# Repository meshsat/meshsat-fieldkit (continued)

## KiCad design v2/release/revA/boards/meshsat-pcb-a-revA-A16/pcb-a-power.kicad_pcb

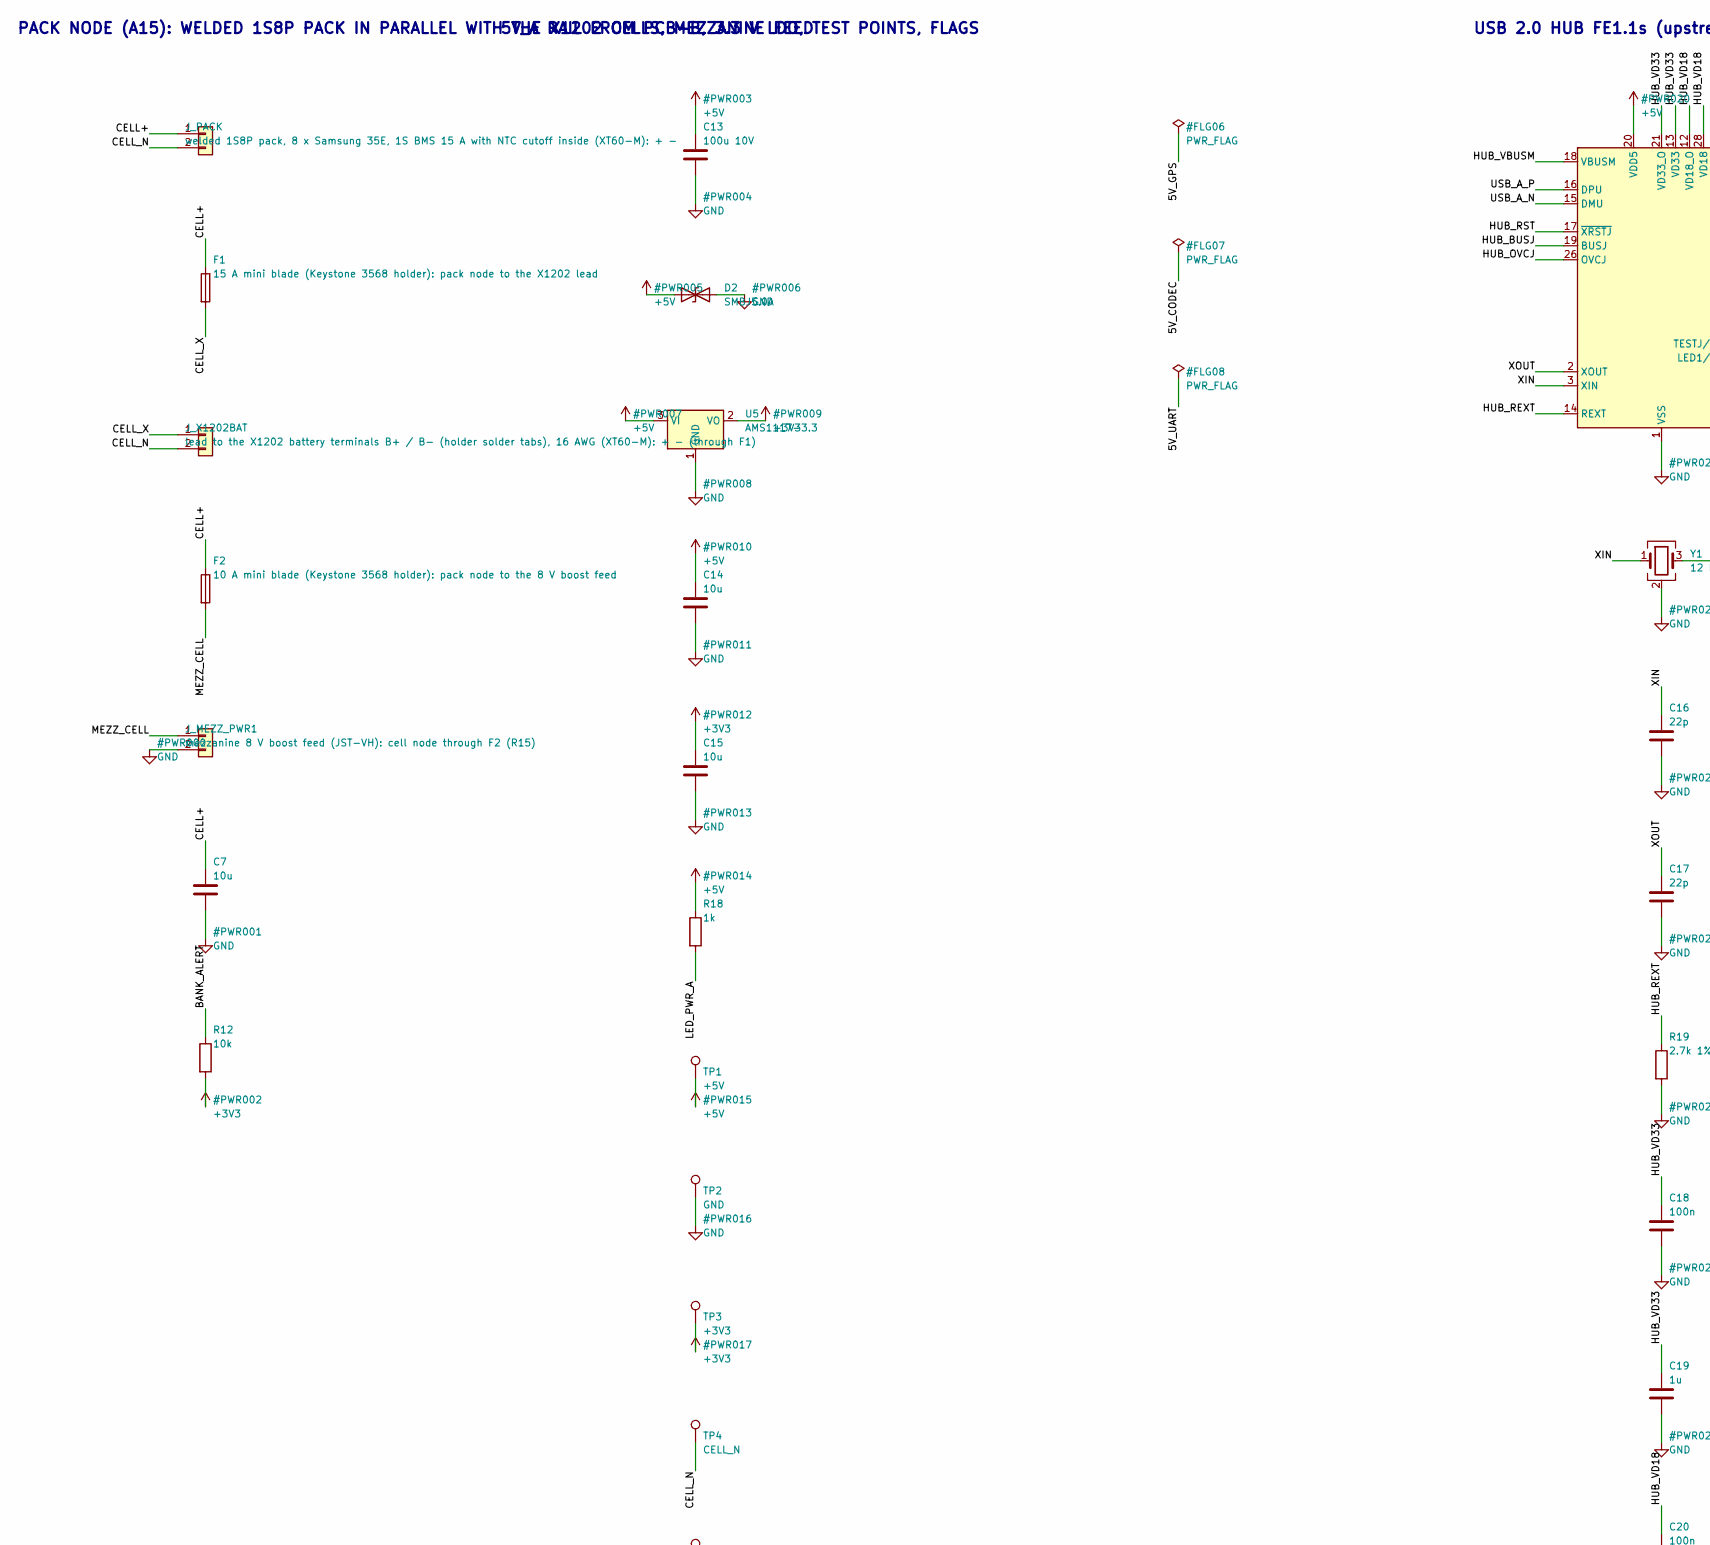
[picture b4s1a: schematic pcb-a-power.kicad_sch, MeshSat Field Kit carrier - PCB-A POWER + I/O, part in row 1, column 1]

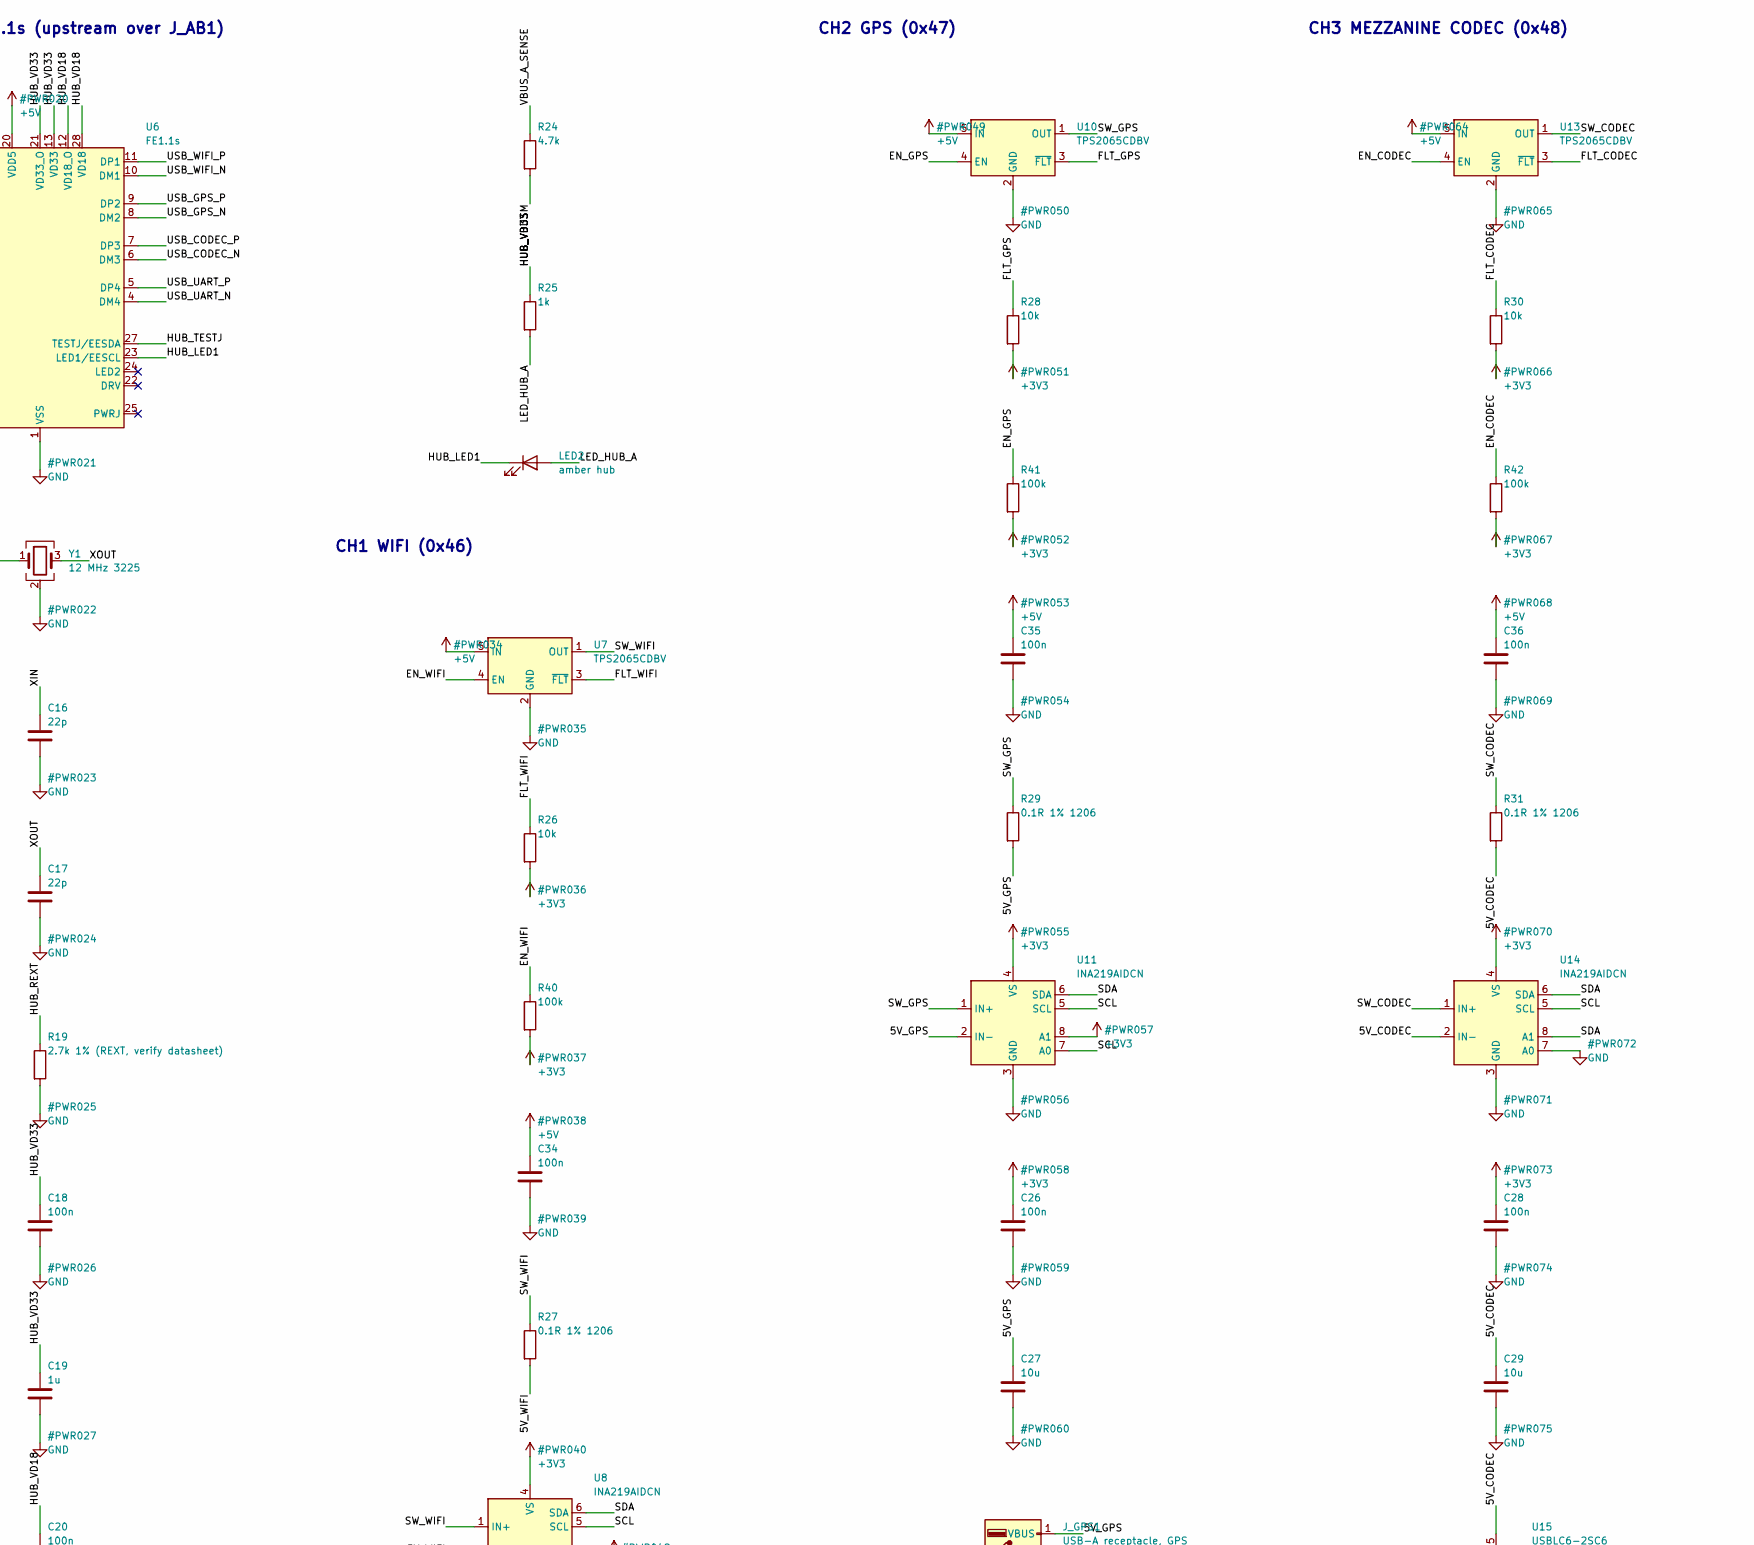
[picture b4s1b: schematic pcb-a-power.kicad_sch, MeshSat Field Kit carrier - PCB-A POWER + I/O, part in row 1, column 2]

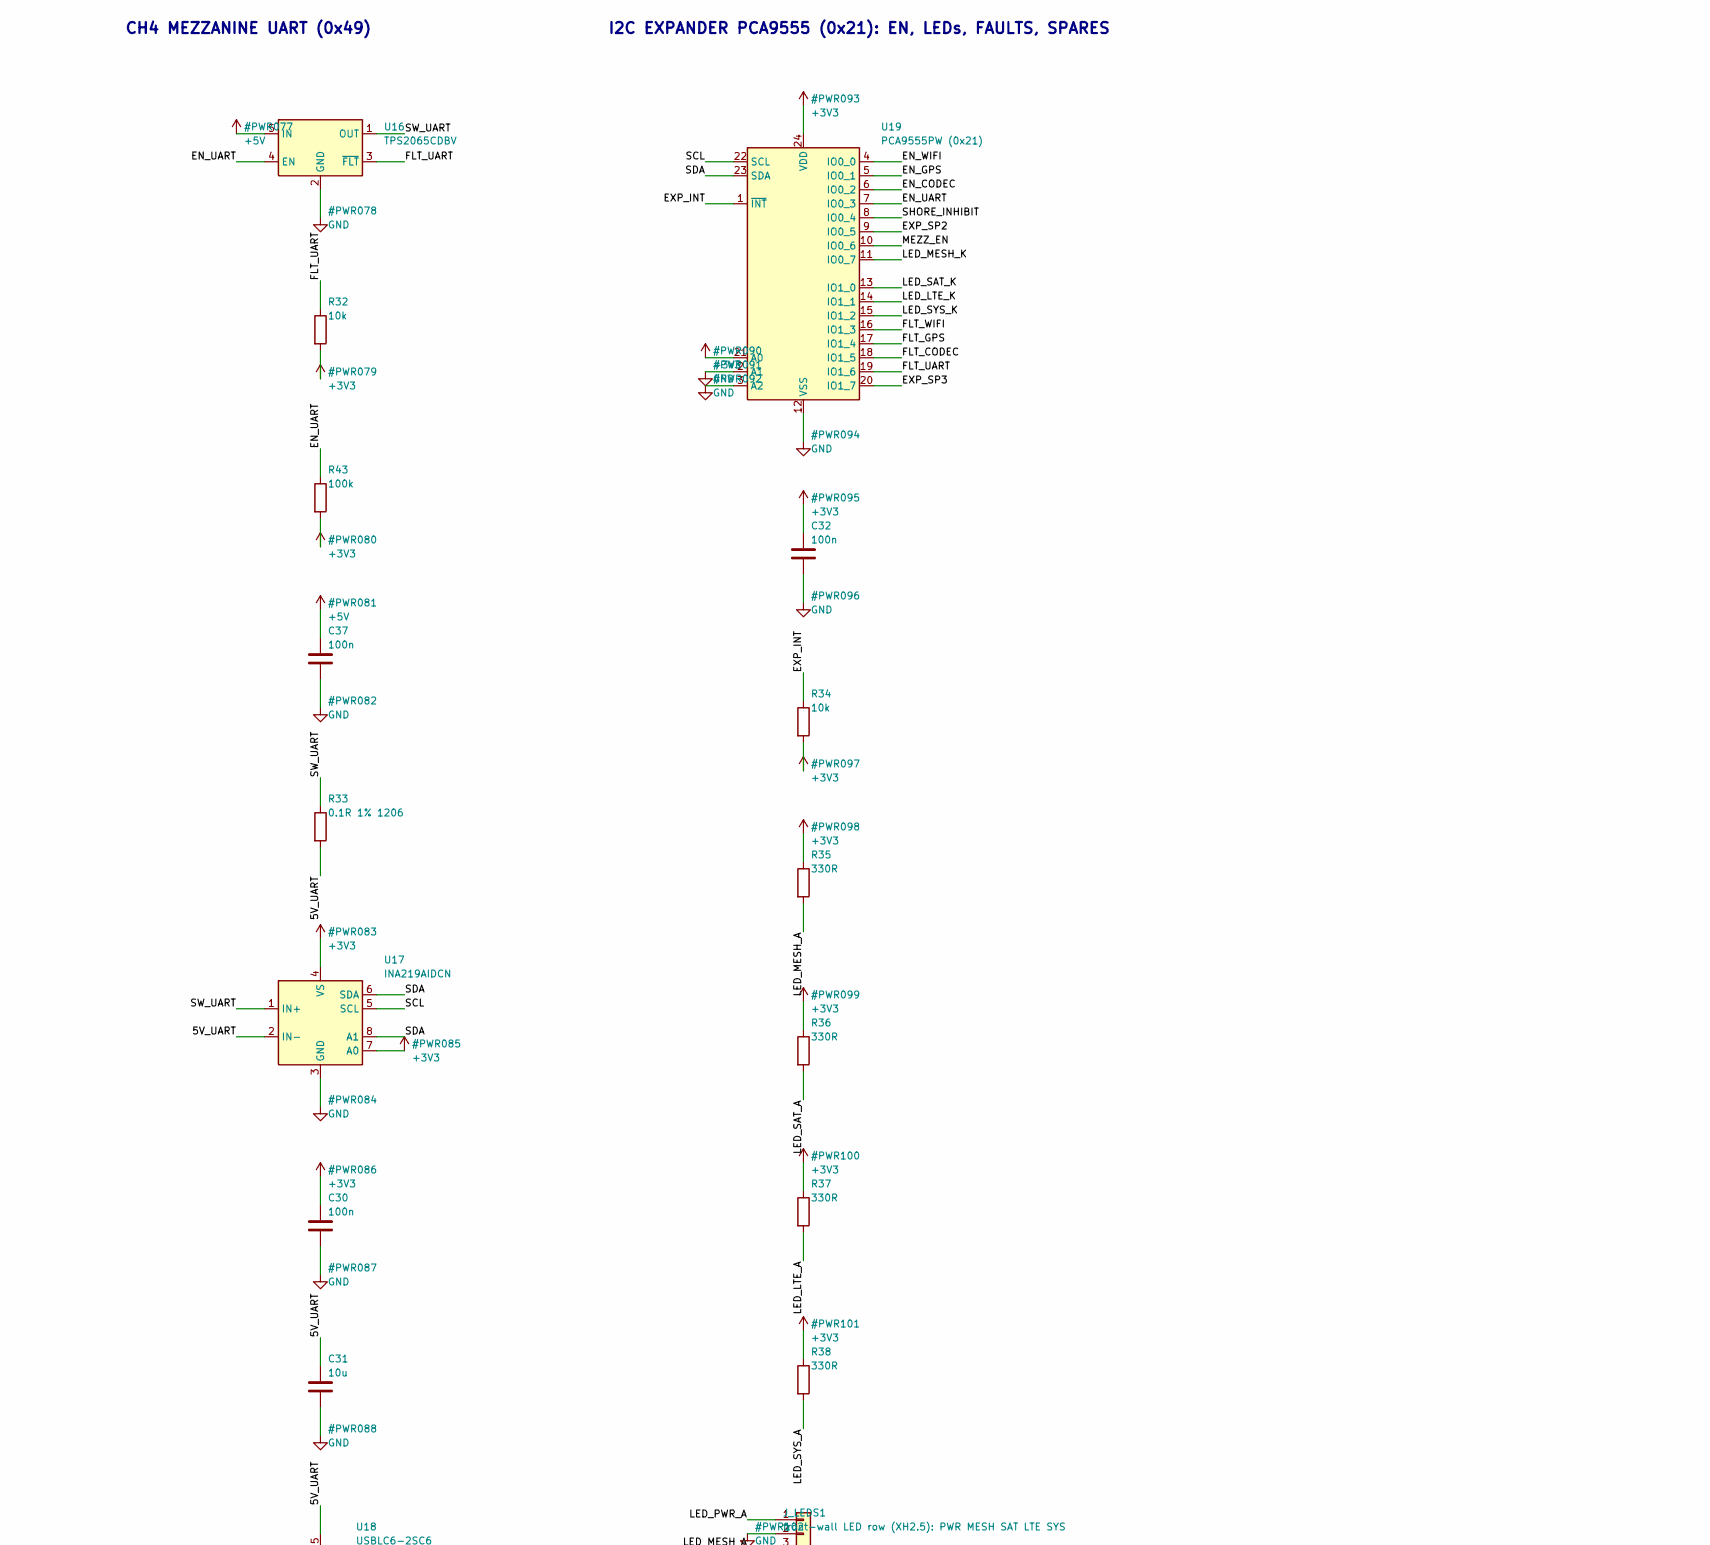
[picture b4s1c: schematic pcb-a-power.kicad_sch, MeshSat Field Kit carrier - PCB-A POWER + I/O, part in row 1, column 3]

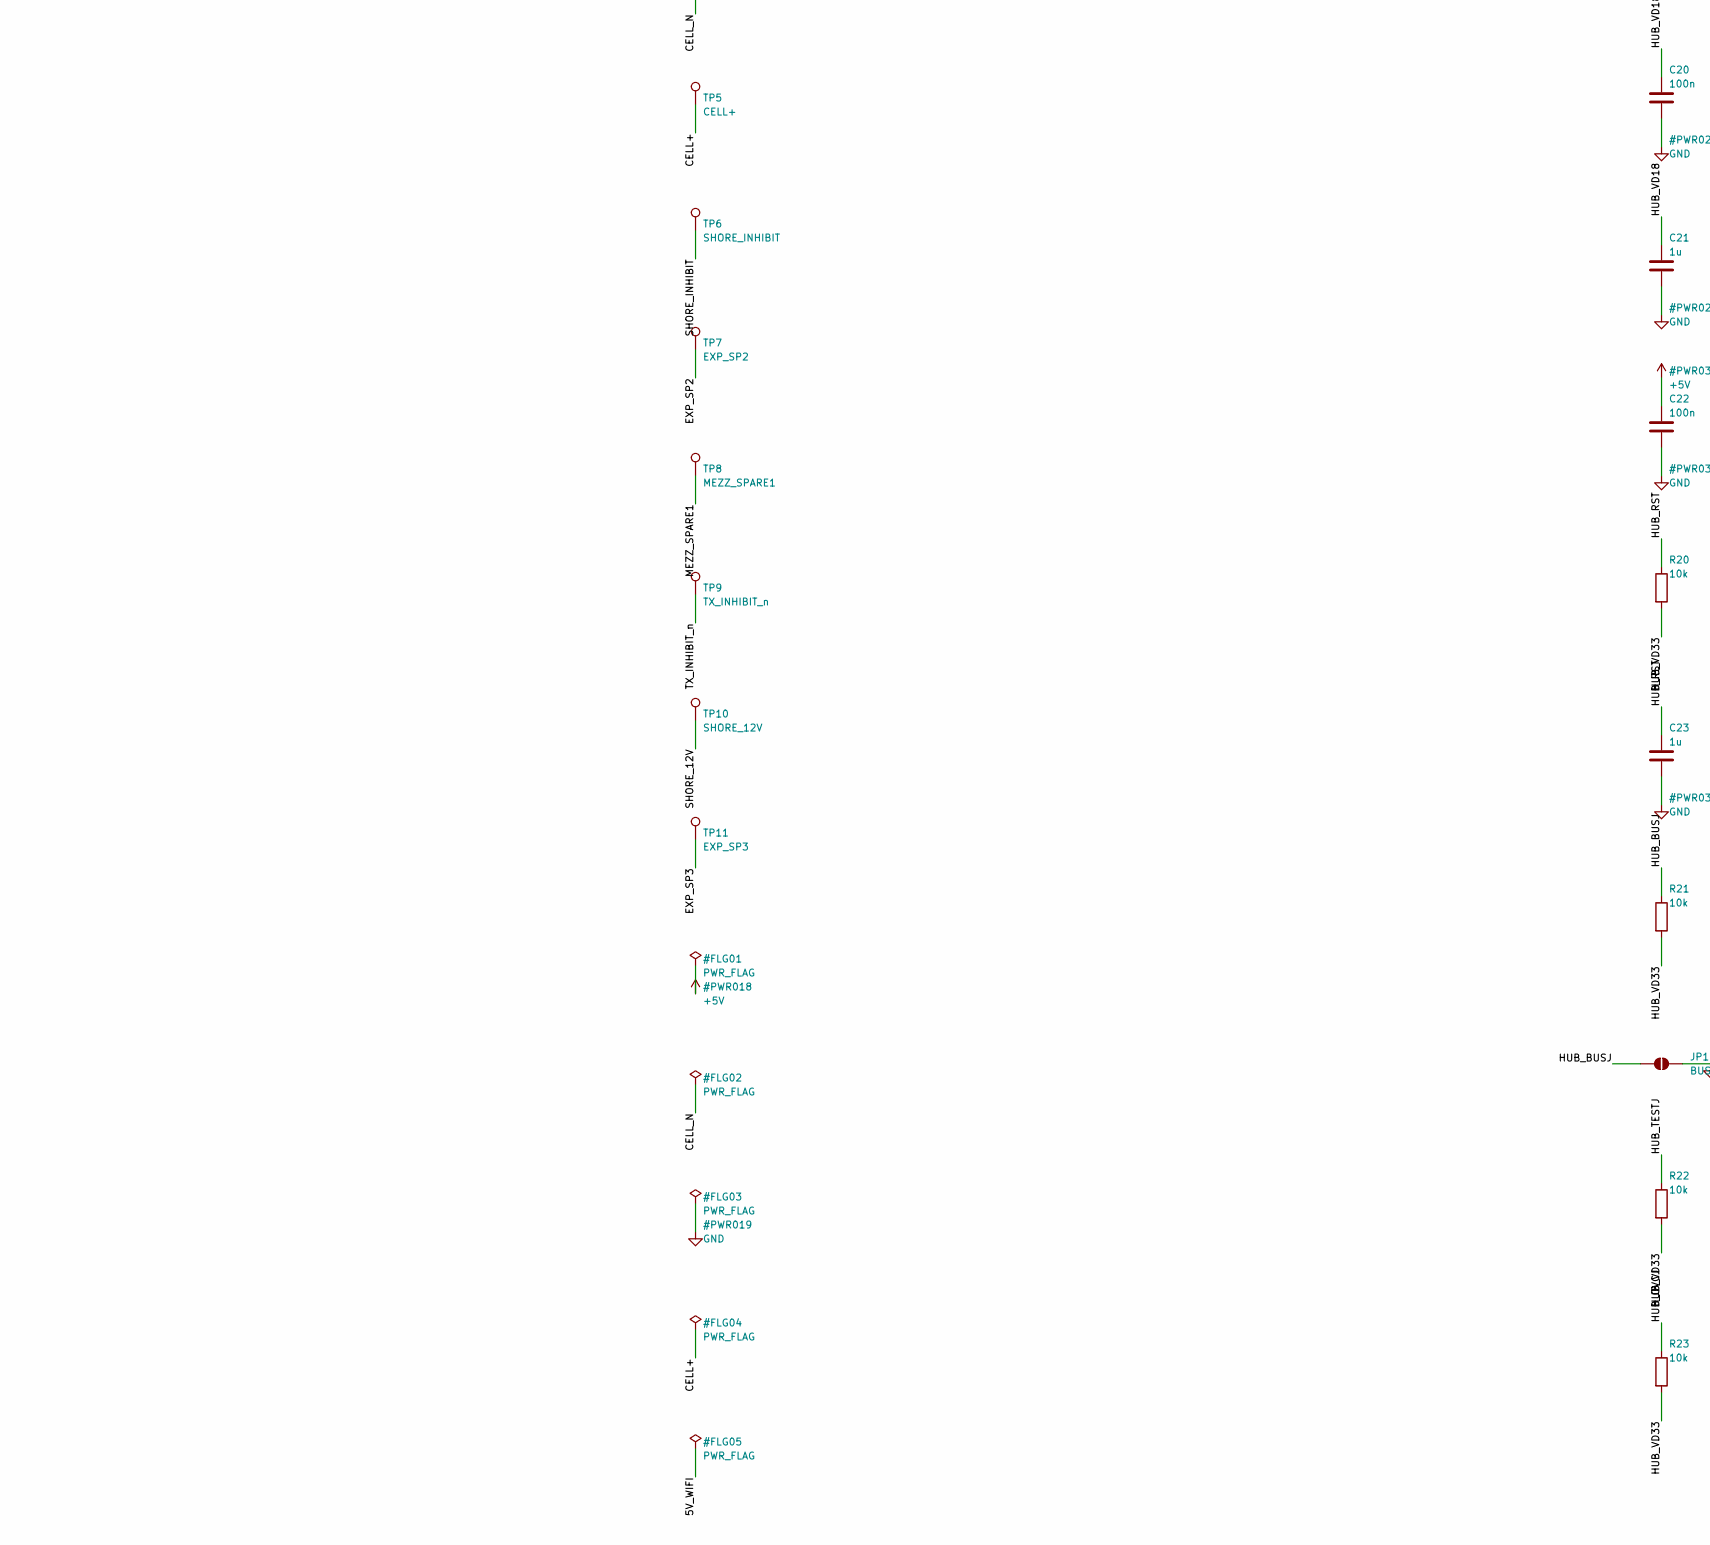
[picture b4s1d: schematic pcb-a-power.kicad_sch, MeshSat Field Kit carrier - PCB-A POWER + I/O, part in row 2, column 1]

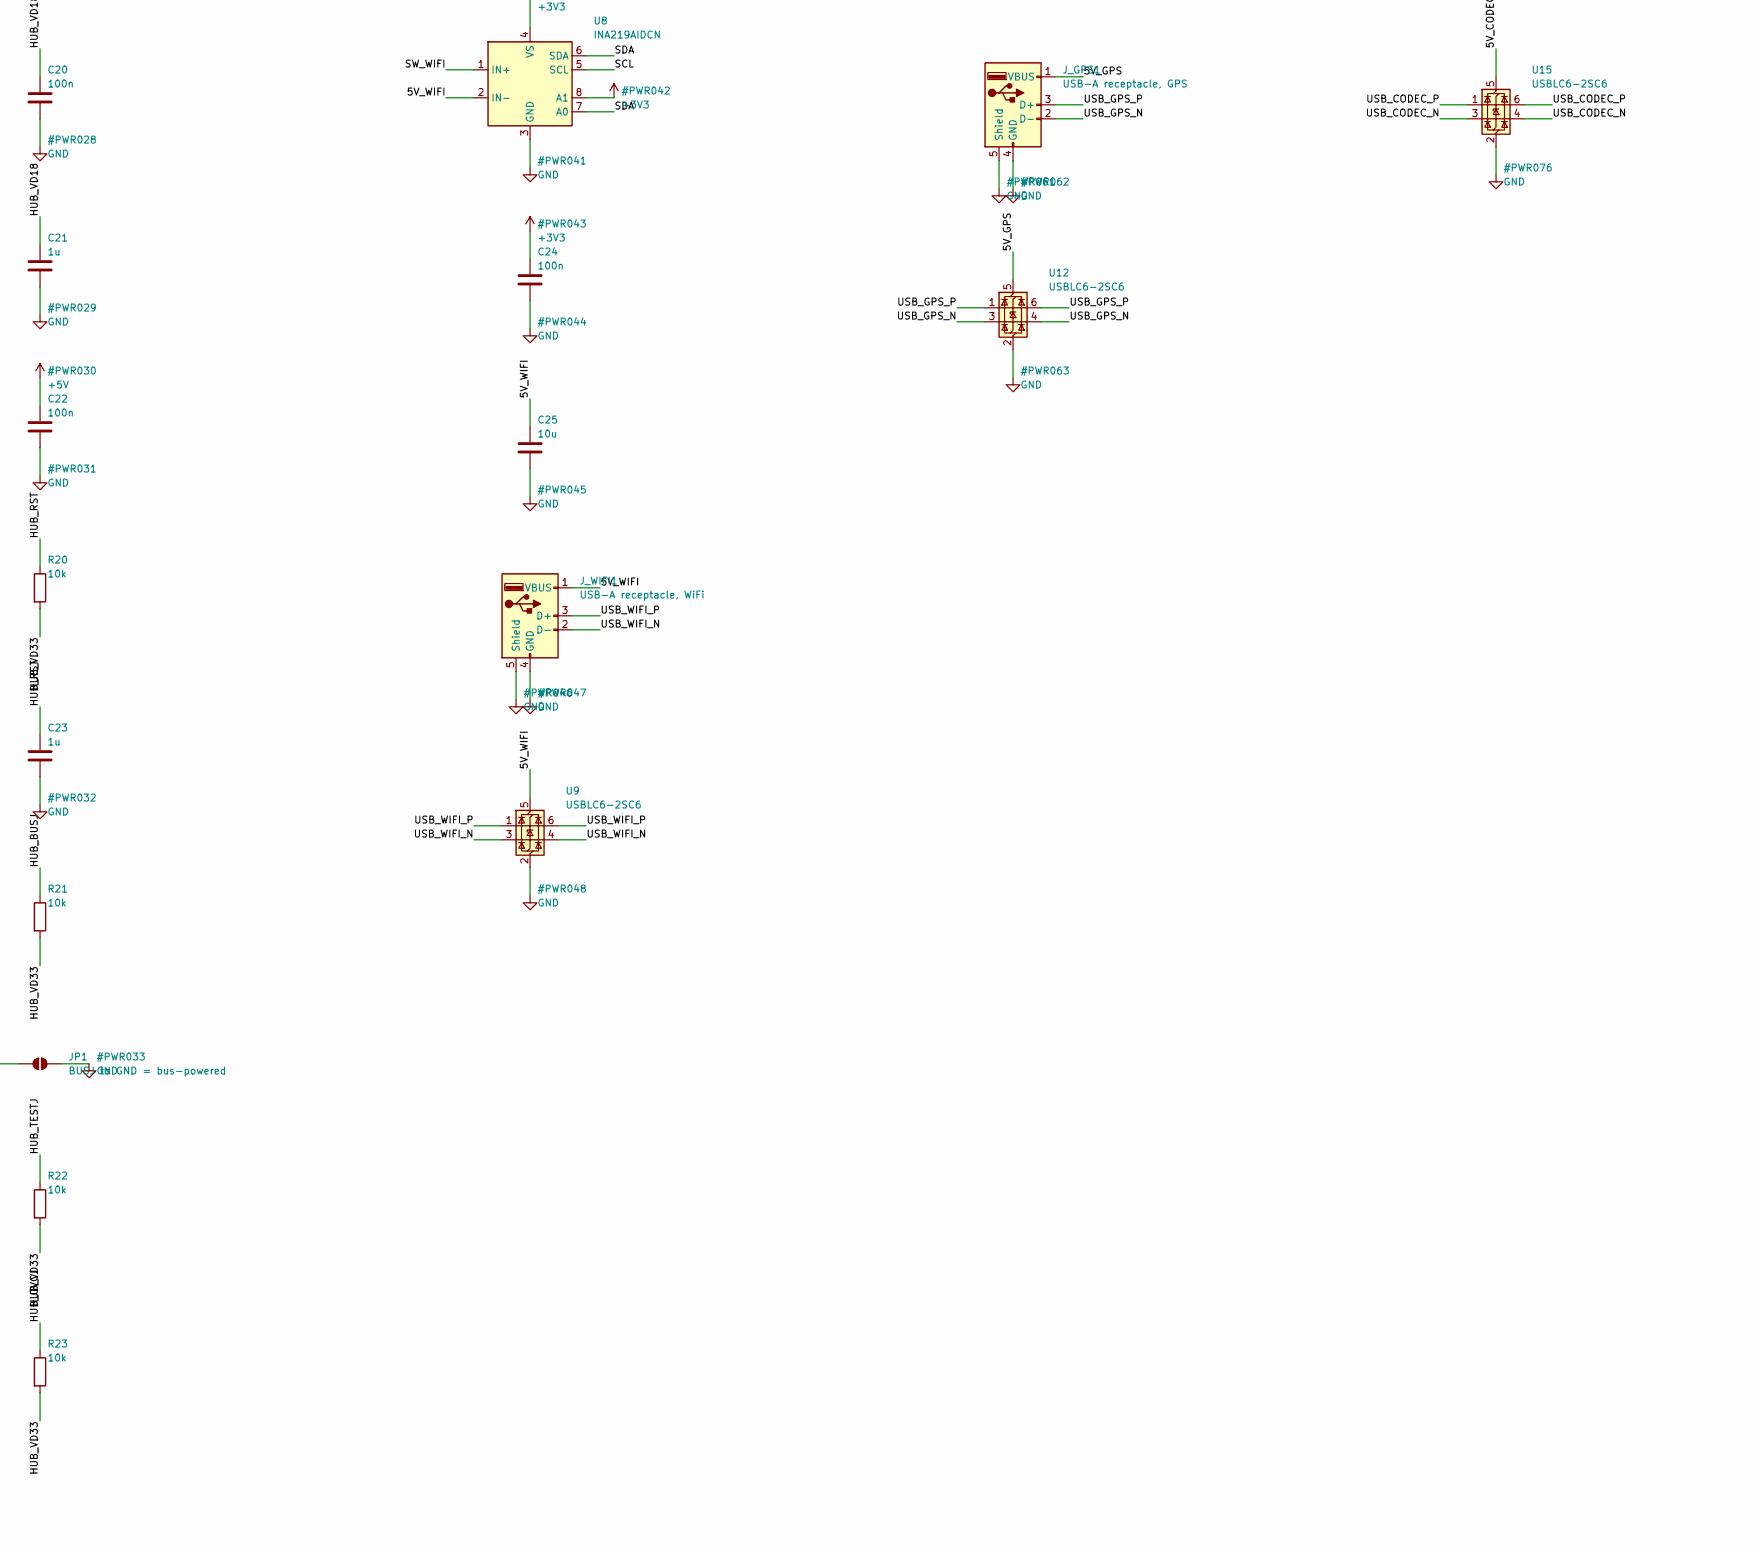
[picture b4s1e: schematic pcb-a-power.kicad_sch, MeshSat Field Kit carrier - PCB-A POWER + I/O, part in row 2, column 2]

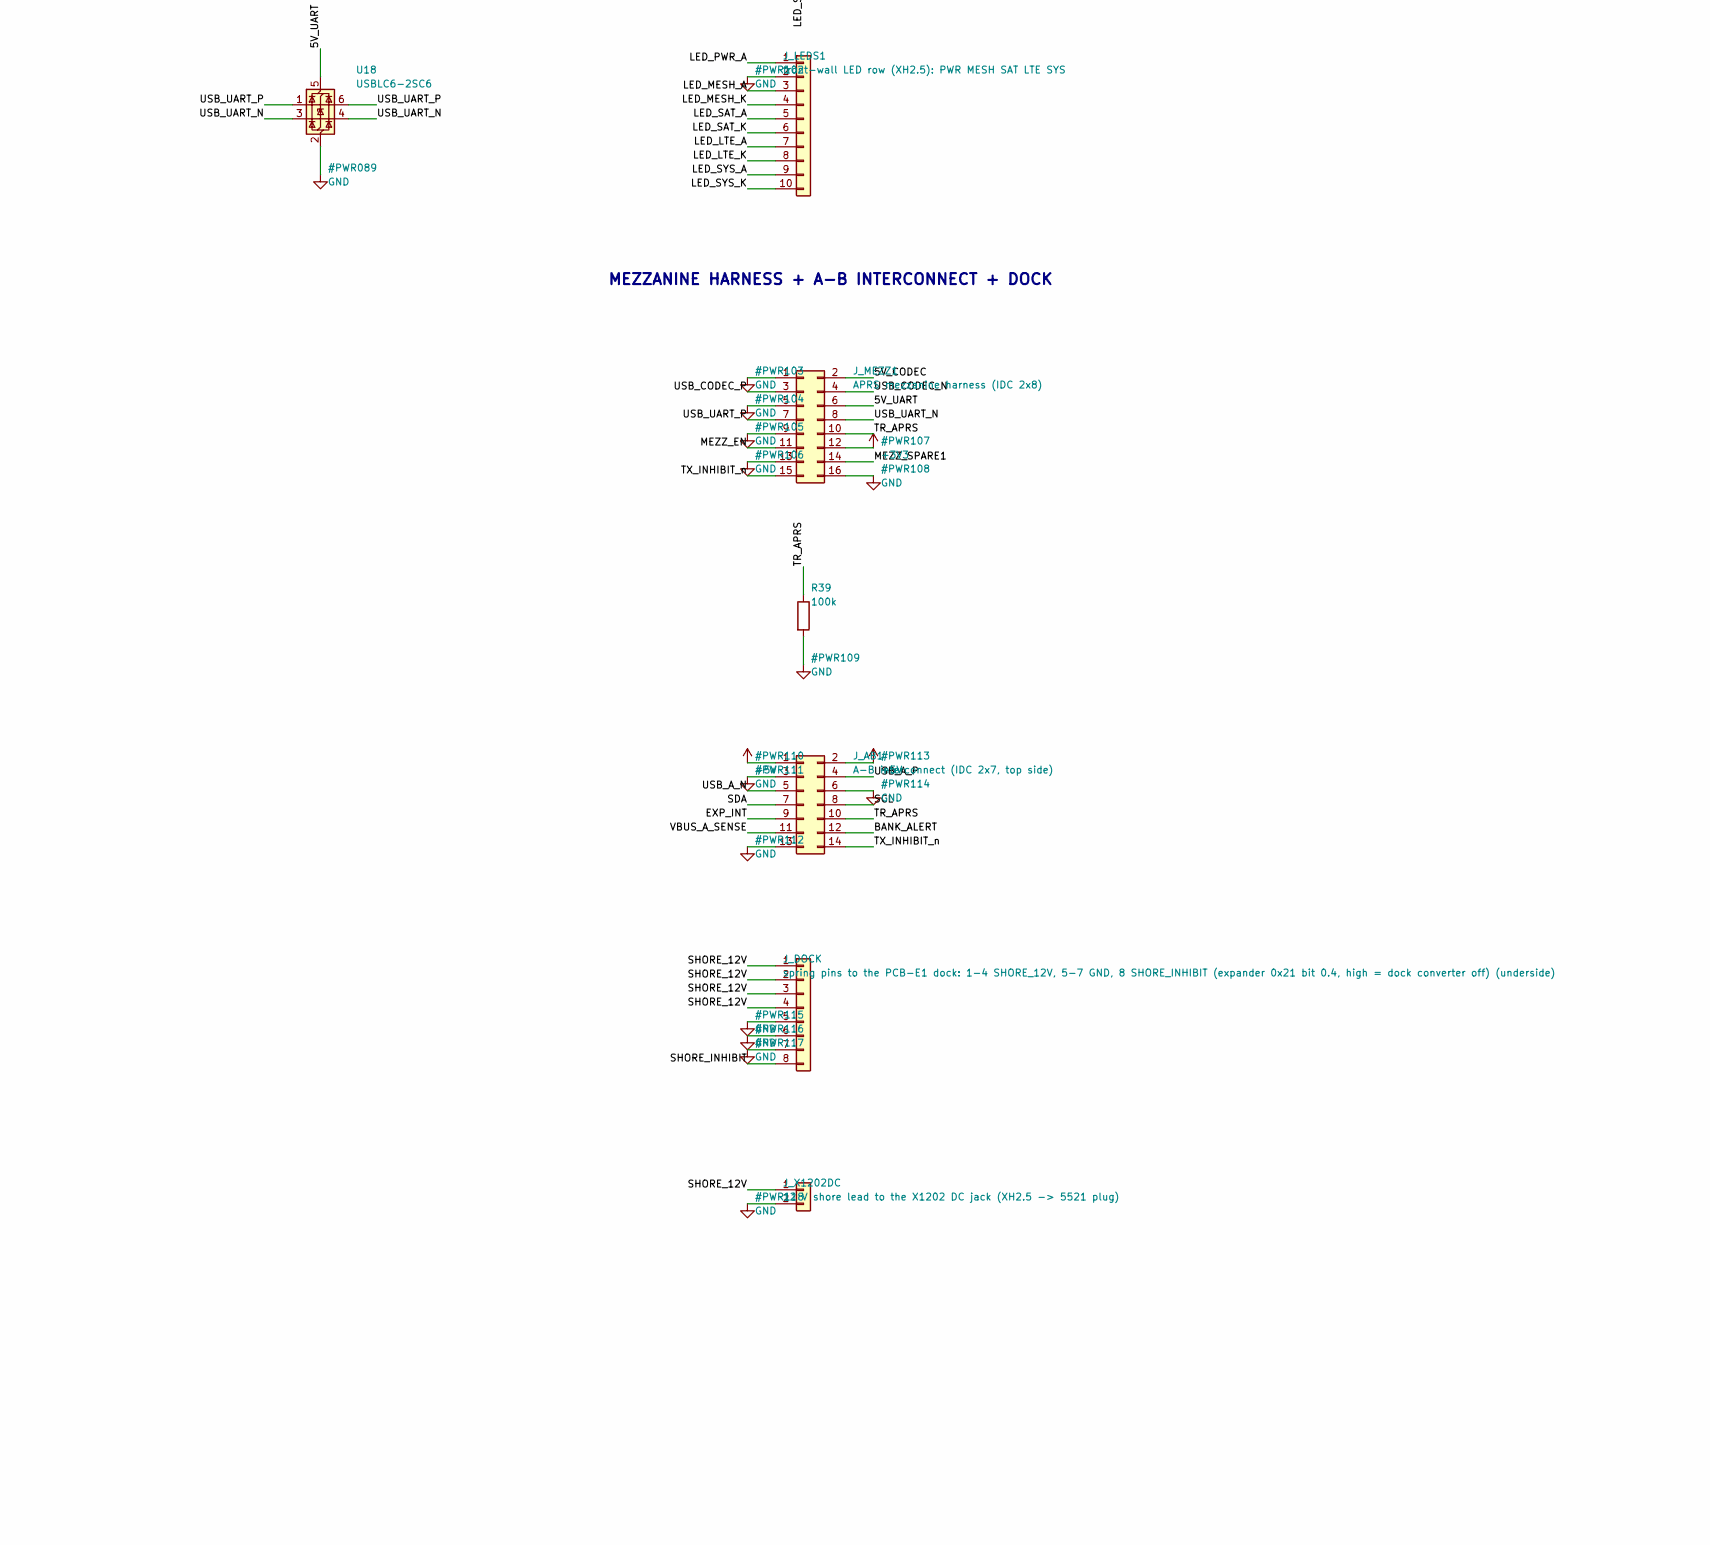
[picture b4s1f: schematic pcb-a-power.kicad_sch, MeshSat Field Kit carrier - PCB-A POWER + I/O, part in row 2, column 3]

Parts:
C7, C14, C15, C25, C27, C29, C31: 10u; C_0805_2012Metric
C13: 100u 10V; C_1206_3216Metric
C16, C17: 22p; C_0603_1608Metric
C18, C20, C22, C24, C26, C28, C30, C32, C34, C35, C36, C37: 100n; C_0603_1608Metric
C19, C21, C23: 1u; C_0603_1608Metric
D2: SMBJ5.0A; D_SMB
F1: 15 A mini blade (Keystone 3568 holder): pack node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; Fuseholder_Blade_Mini_Keystone_3568
F2: 10 A mini blade (Keystone 3568 holder): pack node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; Fuseholder_Blade_Mini_Keystone_3568
JP1: BUSJ to GND = bus-powered; SolderJumper-2_P1.3mm_Open_RoundedPad1.0x1.5mm
J_AB1: A-B interconnect (IDC 2x7, top side); IDC-Header_2x07_P2.54mm_Vertical
J_DOCK: spring pins to the PCB-E1 dock: 1-4 SHORE_12V, 5-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; PogoPins_2x4
J_GPS1: USB-A receptacle, GPS; USB_A_Stewart_SS-52100-001_Horizontal
J_LEDS1: front-wall LED row (XH2.5): PWR MESH SAT LTE SYS; JST_XH_B10B-XH-A_1x10_P2.50mm_Vertical
J_MEZZ1: APRS mezzanine harness (IDC 2x8); IDC-Header_2x08_P2.54mm_Vertical
J_MEZZ_PWR1: mezzanine 8 V boost feed (JST-VH): cell node thro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; JST_VH_B2P-VH_1x02_P3.96mm_Vertical
J_PACK: welded 1S8P pack, 8 x Samsung 35E, 1S BMS 15 A wi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; AMASS_XT60-M_1x02_P7.20mm_Vertical
J_WIFI1: USB-A receptacle, WiFi; USB_A_Stewart_SS-52100-001_Horizontal
J_X1202BAT: lead to the X1202 battery terminals B+ / B- (hold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; AMASS_XT60-M_1x02_P7.20mm_Vertical
J_X1202DC: 12 V shore lead to the X1202 DC jack (XH2.5 -> 55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; JST_XH_B2B-XH-A_1x02_P2.50mm_Vertical
LED2: amber hub; LED_0603_1608Metric
R12, R20, R21, R22, R23, R26, R28, R30, R32, R34: 10k; R_0603_1608Metric
R18, R25: 1k; R_0603_1608Metric
R19: 2.7k 1% (REXT, verify datasheet); R_0603_1608Metric
R24: 4.7k; R_0603_1608Metric
R27, R29, R31, R33: 0.1R 1% 1206; R_1206_3216Metric
R35, R36, R37, R38: 330R; R_0603_1608Metric
R39, R40, R41, R42, R43: 100k; R_0603_1608Metric
TP1: +5V; TestPoint_Pad_D1.5mm
TP2: GND; TestPoint_Pad_D1.5mm
TP3: +3V3; TestPoint_Pad_D1.5mm
TP4: CELL_N; TestPoint_Pad_D1.5mm
TP5: CELL+; TestPoint_Pad_D1.5mm
TP6: SHORE_INHIBIT; TestPoint_Pad_D1.5mm
TP7: EXP_SP2; TestPoint_Pad_D1.5mm
TP8: MEZZ_SPARE1; TestPoint_Pad_D1.5mm
TP9: TX_INHIBIT_n; TestPoint_Pad_D1.5mm
TP10: SHORE_12V; TestPoint_Pad_D1.5mm
TP11: EXP_SP3; TestPoint_Pad_D1.5mm
U5: AMS1117-3.3; SOT-223-3_TabPin2
U6: FE1.1s; SSOP-28_5.3x10.2mm_P0.65mm; LCSC C2848
U7, U10, U13, U16: TPS2065CDBV; SOT-23-6
U8, U11, U14, U17: INA219AIDCN; SOT-23-8; LCSC C138024
U9, U12, U15, U18: USBLC6-2SC6; SOT-23-6; LCSC C7519
U19: PCA9555PW (0x21); TSSOP-24_4.4x7.8mm_P0.65mm; LCSC C5626
Y1: 12 MHz 3225; Crystal_SMD_3225-4Pin_3.2x2.5mm

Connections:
+3V3: C15.1, C24.1, C26.1, C28.1, C30.1, C32.1, J_MEZZ1.12, R12.2, R26.2, R28.2, R30.2, R32.2, R34.2, R35.1, R36.1, R37.1, R38.1, R40.2, R41.2, R42.2, R43.2, TP3.1, U5.2 (VO), U8.4 (VS), U8.8 (A1), U11.4 (VS), U11.8 (A1), U14.4 (VS), U17.4 (VS), U17.7 (A0), U19.21 (A0), U19.24 (VDD)
+5V: C13.1, C14.1, C22.1, C34.1, C35.1, C36.1, C37.1, D2.1 (A1), J_AB1.1, J_AB1.2, R18.1, TP1.1, U5.3 (VI), U6.20 (VDD5), U7.5 (IN), U10.5 (IN), U13.5 (IN), U16.5 (IN)
/5V_CODEC: C29.1, J_MEZZ1.2, R31.2, U14.2 (IN-), U15.5 (VBUS)
/5V_GPS: C27.1, J_GPS1.1 (VBUS), R29.2, U11.2 (IN-), U12.5 (VBUS)
/5V_UART: C31.1, J_MEZZ1.6, R33.2, U17.2 (IN-), U18.5 (VBUS)
/5V_WIFI: C25.1, J_WIFI1.1 (VBUS), R27.2, U8.2 (IN-), U9.5 (VBUS)
/BANK_ALERT: J_AB1.12, R12.1
/CELL+: C7.1, F1.1, F2.1, J_PACK.1, TP5.1
/CELL_N: J_PACK.2, J_X1202BAT.2, TP4.1
/CELL_X: F1.2, J_X1202BAT.1
/EN_CODEC: R42.1, U13.4 (EN), U19.6 (IO0_2)
/EN_GPS: R41.1, U10.4 (EN), U19.5 (IO0_1)
/EN_UART: R43.1, U16.4 (EN), U19.7 (IO0_3)
/EN_WIFI: R40.1, U7.4 (EN), U19.4 (IO0_0)
/EXP_INT: J_AB1.9, R34.1, U19.1 (~INT)
/EXP_SP2: TP7.1, U19.9 (IO0_5)
/EXP_SP3: TP11.1, U19.20 (IO1_7)
/FLT_CODEC: R30.1, U13.3 (~FLT), U19.18 (IO1_5)
/FLT_GPS: R28.1, U10.3 (~FLT), U19.17 (IO1_4)
/FLT_UART: R32.1, U16.3 (~FLT), U19.19 (IO1_6)
/FLT_WIFI: R26.1, U7.3 (~FLT), U19.16 (IO1_3)
/HUB_BUSJ: JP1.1 (A), R21.1, U6.19 (BUSJ)
/HUB_LED1: LED2.1 (K), U6.23 (LED1/EESCL)
/HUB_OVCJ: R23.1, U6.26 (OVCJ)
/HUB_REXT: R19.1, U6.14 (REXT)
/HUB_RST: C23.1, R20.1, U6.17 (~XRSTJ)
/HUB_TESTJ: R22.1, U6.27 (TESTJ/EESDA)
/HUB_VBUSM: R24.2, U6.18 (VBUSM)
/HUB_VD18: C20.1, C21.1, U6.12 (VD18_O), U6.28 (VD18)
/HUB_VD33: C18.1, C19.1, R20.2, R21.2, R22.2, R23.2, R25.1, U6.13 (VD33), U6.21 (VD33_O)
/LED_HUB_A: LED2.2 (A), R25.2
/LED_LTE_A: J_LEDS1.7, R37.2
/LED_LTE_K: J_LEDS1.8, U19.14 (IO1_1)
/LED_MESH_A: J_LEDS1.3, R35.2
/LED_MESH_K: J_LEDS1.4, U19.11 (IO0_7)
/LED_PWR_A: J_LEDS1.1, R18.2
/LED_SAT_A: J_LEDS1.5, R36.2
/LED_SAT_K: J_LEDS1.6, U19.13 (IO1_0)
/LED_SYS_A: J_LEDS1.9, R38.2
/LED_SYS_K: J_LEDS1.10, U19.15 (IO1_2)
/MEZZ_CELL: F2.2, J_MEZZ_PWR1.1
/MEZZ_EN: J_MEZZ1.11, U19.10 (IO0_6)
/MEZZ_SPARE1: J_MEZZ1.14, TP8.1
/SCL: J_AB1.8, U8.5 (SCL), U11.5 (SCL), U11.7 (A0), U14.5 (SCL), U17.5 (SCL), U19.22 (SCL)
/SDA: J_AB1.7, U8.6 (SDA), U8.7 (A0), U11.6 (SDA), U14.6 (SDA), U14.8 (A1), U17.6 (SDA), U17.8 (A1), U19.23 (SDA)
/SHORE_12V: J_DOCK.1, J_DOCK.2, J_DOCK.3, J_DOCK.4, J_X1202DC.1, TP10.1
/SHORE_INHIBIT: J_DOCK.8, TP6.1, U19.8 (IO0_4)
/SW_CODEC: R31.1, U13.1 (OUT), U14.1 (IN+)
/SW_GPS: R29.1, U10.1 (OUT), U11.1 (IN+)
/SW_UART: R33.1, U16.1 (OUT), U17.1 (IN+)
/SW_WIFI: R27.1, U7.1 (OUT), U8.1 (IN+)
/TR_APRS: J_AB1.10, J_MEZZ1.10, R39.1
/TX_INHIBIT_n: J_AB1.14, J_MEZZ1.15, TP9.1
/USB_A_N: J_AB1.5, U6.15 (DMU)
/USB_A_P: J_AB1.4, U6.16 (DPU)
/USB_CODEC_N: J_MEZZ1.4, U6.6 (DM3), U15.3 (I/O2), U15.4 (I/O2)
/USB_CODEC_P: J_MEZZ1.3, U6.7 (DP3), U15.1 (I/O1), U15.6 (I/O1)
/USB_GPS_N: J_GPS1.2 (D-), U6.8 (DM2), U12.3 (I/O2), U12.4 (I/O2)
/USB_GPS_P: J_GPS1.3 (D+), U6.9 (DP2), U12.1 (I/O1), U12.6 (I/O1)
/USB_UART_N: J_MEZZ1.8, U6.4 (DM4), U18.3 (I/O2), U18.4 (I/O2)
/USB_UART_P: J_MEZZ1.7, U6.5 (DP4), U18.1 (I/O1), U18.6 (I/O1)
/USB_WIFI_N: J_WIFI1.2 (D-), U6.10 (DM1), U9.3 (I/O2), U9.4 (I/O2)
/USB_WIFI_P: J_WIFI1.3 (D+), U6.11 (DP1), U9.1 (I/O1), U9.6 (I/O1)
/VBUS_A_SENSE: J_AB1.11, R24.1
/XIN: C16.1, U6.3 (XIN), Y1.1
/XOUT: C17.1, U6.2 (XOUT), Y1.3
GND: C7.2, C13.2, C14.2, C15.2, C16.2, C17.2, C18.2, C19.2, C20.2, C21.2, C22.2, C23.2, C24.2, C25.2, C26.2, C27.2, C28.2, C29.2, C30.2, C31.2, C32.2, C34.2, C35.2, C36.2, C37.2, D2.2 (A2), JP1.2 (B), J_AB1.3, J_AB1.6, J_AB1.13, J_DOCK.5, J_DOCK.6, J_DOCK.7, J_GPS1.4 (GND), J_GPS1.5 (Shield), J_LEDS1.2, J_MEZZ1.1, J_MEZZ1.5, J_MEZZ1.9, J_MEZZ1.13, J_MEZZ1.16, J_MEZZ_PWR1.2, J_WIFI1.4 (GND), J_WIFI1.5 (Shield), J_X1202DC.2, R19.2, R39.2, TP2.1, U5.1 (GND), U6.1 (VSS), U7.2 (GND), U8.3 (GND), U9.2 (GND), U10.2 (GND), U11.3 (GND), U12.2 (GND), U13.2 (GND), U14.3 (GND), U14.7 (A0), U15.2 (GND), U16.2 (GND), U17.3 (GND), U18.2 (GND), U19.2 (A1), U19.3 (A2), U19.12 (VSS), Y1.2 (G), Y1.4 (G)

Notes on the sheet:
PACK NODE (A15): WELDED 1S8P PACK IN PARALLEL WITH THE X1202 CELLS, MEZZANINE FEED
5V_A RAIL FROM PCB-B, 3.3 V LDO, TEST POINTS, FLAGS
USB 2.0 HUB FE1.1s (upstream over J_AB1)
CH1 WIFI (0x46)
CH2 GPS (0x47)
CH3 MEZZANINE CODEC (0x48)
CH4 MEZZANINE UART (0x49)
I2C EXPANDER PCA9555 (0x21): EN, LEDs, FAULTS, SPARES
MEZZANINE HARNESS + A-B INTERCONNECT + DOCK

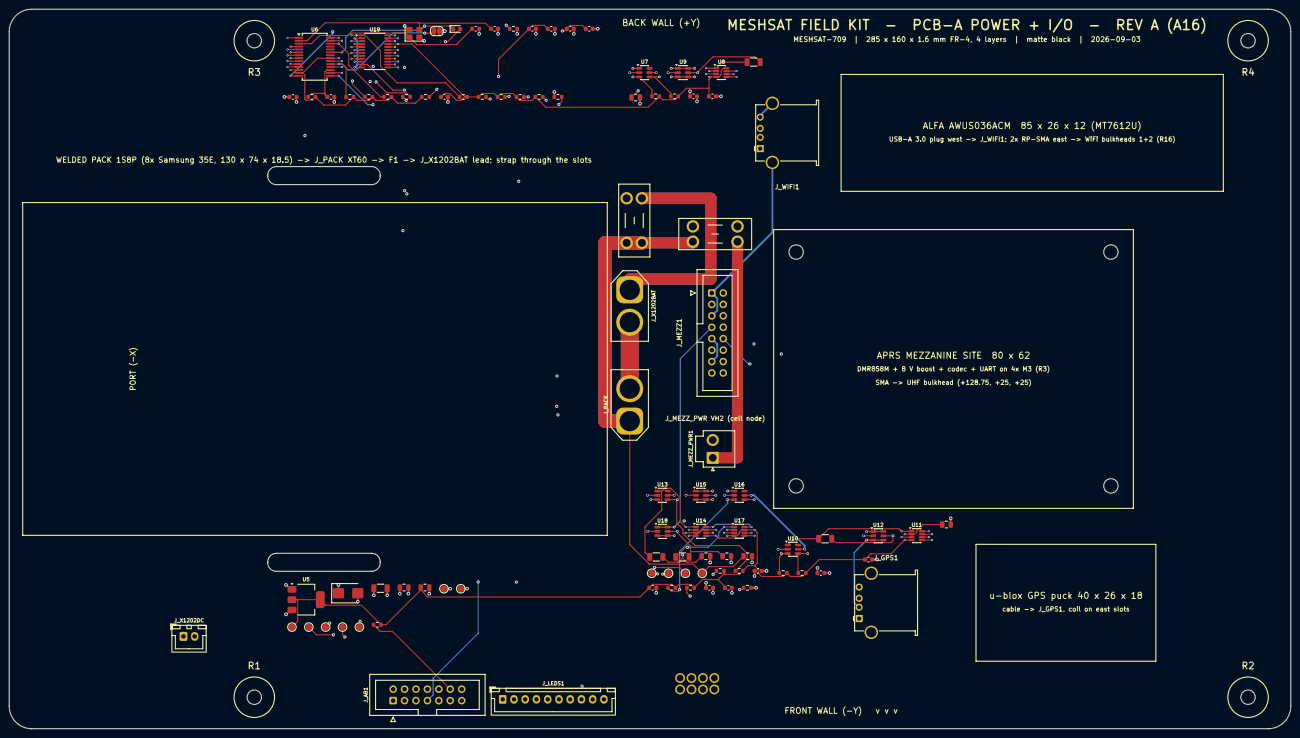
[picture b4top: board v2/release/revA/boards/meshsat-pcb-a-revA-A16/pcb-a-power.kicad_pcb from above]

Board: 4 copper layers, 285.0 x 160.0 mm, 113 parts (1 on the bottom side), 67 nets.

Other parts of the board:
H1: M3 rod R1; MountingHole_3.2mm_M3
H2: M3 rod R2; MountingHole_3.2mm_M3
H3: M3 rod R3; MountingHole_3.2mm_M3
H4: M3 rod R4; MountingHole_3.2mm_M3
H5, H6, H7, H8: M3 standoff, mezzanine; MountingHole_3.2mm_M3
S_GPS1, S_GPS2, S_GPS3, S_GPS4: tie slot; Slot_5x1.8_NPTH
S_GPSC1, S_GPSC2, S_GPSC3: cable coil tie; Slot_5x1.8_NPTH
S_WIFI1, S_WIFI2, S_WIFI3, S_WIFI4: tie slot; Slot_5x1.8_NPTH
